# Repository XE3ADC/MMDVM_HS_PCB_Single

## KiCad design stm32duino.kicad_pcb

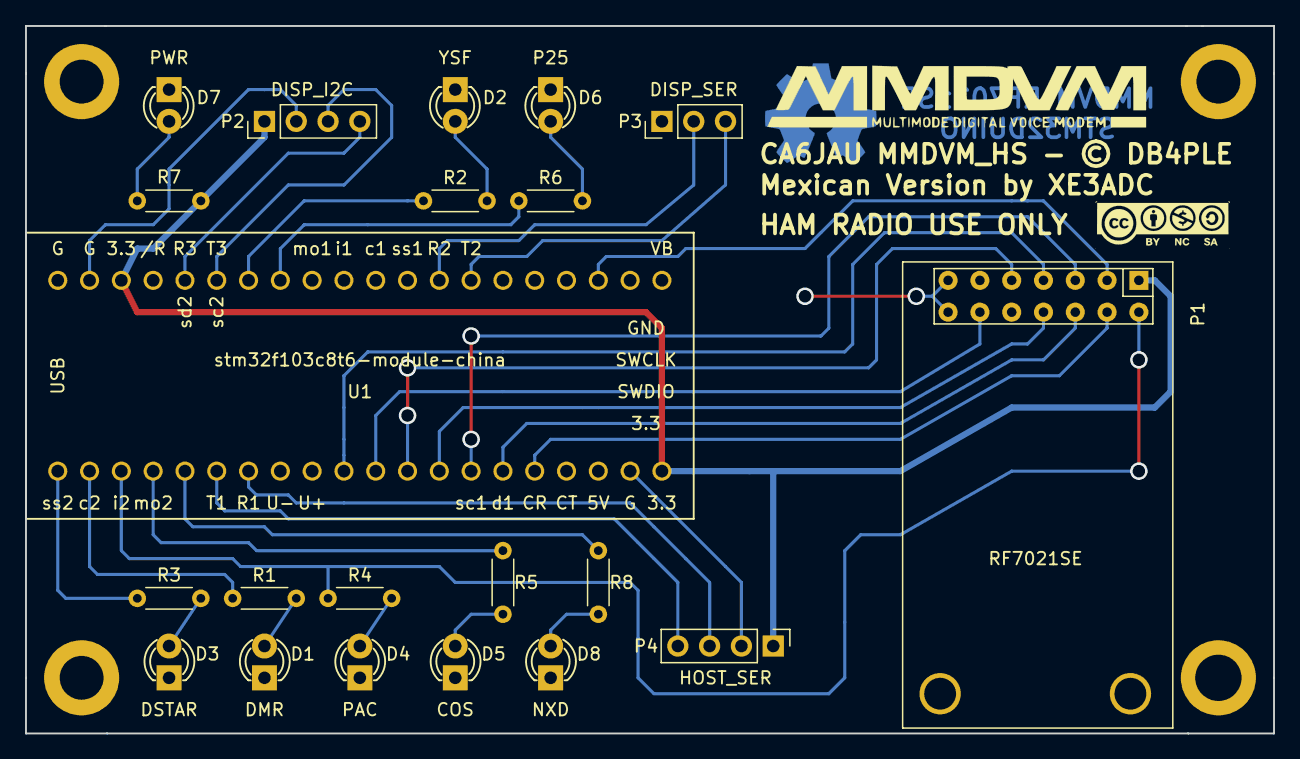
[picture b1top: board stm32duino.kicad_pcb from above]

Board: 2 copper layers, 99.7 x 56.5 mm, 25 parts (0 on the bottom side), 31 nets.

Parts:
D1: DMR; LED-3MM
D2: YSF; LED-3MM
D3: DSTAR; LED-3MM
D4: PAC; LED-3MM
D5: COS; LED-3MM
D6: P25; LED-3MM
D7: PWR; LED-3MM
D8: NXD; LED-3MM
MH1, MH2, MH3: D=3.5mm; MountingHole_3.5mm_Pad
MH4: D=3.5mm; MountingHole_3.7mm_Pad
P1: RF7021SE; RF7021SE_Breakout
P2: DISP_I2C; Pin_Header_Straight_1x04_Pitch2.54mm
P3: DISP_SER; Pin_Header_Straight_1x03_Pitch2.54mm
P4: HOST_SER; Pin_Header_Straight_1x04_Pitch2.54mm
R1, R2, R3, R4, R5, R6, R7, R8: 1K5; R_Axial_DIN0204_L3.6mm_D1.6mm_P5.08mm_Horizontal
U1: stm32f103c8t6-module-china

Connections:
+3V3: P1.1, P2.1, P4.1, R7.1, U1.20, U1.38
CE: P1.3, U1.23
CLKOUT: P1.7, U1.10
DATAIN: P1.12, U1.11
DATAOUT: P1.9, U1.12
DISP_RX: P3.2, U1.28
DISP_TX: P3.3, U1.27
GND: D1.1, D2.1, D3.1, D4.1, D5.1, D6.1, D7.1, D8.1, MH1.1, MH2.2, MH3.3, MH4.4, P1.13, P1.14, P2.2, P3.1, P4.2, U1.19, U1.39, U1.40
HOST_RX: P4.3, U1.7
HOST_TX: P4.4, U1.6
LEDDMR: R1.1, U1.2
LEDDSTAR: R3.1, U1.1
LEDNXD: R8.1, U1.5
LEDP25: R6.1, U1.33
LEDYSF: R2.1, U1.34
LED_COS: R5.1, U1.4
unnamed: D1.2, R1.2
unnamed: D2.2, R2.2
unnamed: D3.2, R3.2
unnamed: D4.2, R4.2
unnamed: D5.2, R5.2
unnamed: D6.2, R6.2
unnamed: D7.2, R7.2
unnamed: D8.2, R8.2
unnamed: P2.3, U1.35
unnamed: P2.4, U1.36
PAC: P1.2, R4.1, U1.3
SCLK: P1.8, U1.13
SDATA: P1.5, U1.14
SLE: P1.4, U1.16
SREAD: P1.6, U1.15

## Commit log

2018-04-09 modified for Trhuhole components, added NXD LED.
    Modifications from original Project:
    -Changed LEDs and resistors from SMD to TrhuHole, and facing to the front of the board.
    -Added LED for NXD operation.
    -Increased track width for RF7021SE +3.3 VDC.
    -Modified header connectors orientation for 3D view.
2018-04-09 Updated Schematic with NXD LED
    Printed to PDF file from modified original project schematic, Added a LED and associated resistor D8 and R8.
2018-04-09 Produced PCB Placement PDF.
    Printed as PDF from Kicad
2018-04-09 Produced PCB layout as PDF
    Printed as PDF from KIcad
2018-04-09 Produced PCB layout as PDF
    Kicad back up file from last session
2018-05-09 Added Mounting holes and RF7021 breakout board footprint
    Additions: 3.5mm mounting holes on corners., footprint for RF7021 breakout board, Text labels for CC licensing, model, usage and credits, text labels for LED indicator signals.
2018-05-09 Produced updated PDF files.
    Produced PDF files for: PCB layout and component placement.

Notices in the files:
stm32duino.kicad_pcb:
CA6JAU MMDVM_HS - © DB4PLE
